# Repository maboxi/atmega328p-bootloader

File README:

# Bootloader + Python program for the Atmega328P chip

This project contains a custom bootloader program for the Atmega328P (known for the Arduino family boards) which fulfills basic bootloader functionalities:
- Uploading a program (given by a Intel Hex format file) to the microcontroller
- Verifiying an upload
- Reading the fuse bytes (extended, high, low) and interpreting the values

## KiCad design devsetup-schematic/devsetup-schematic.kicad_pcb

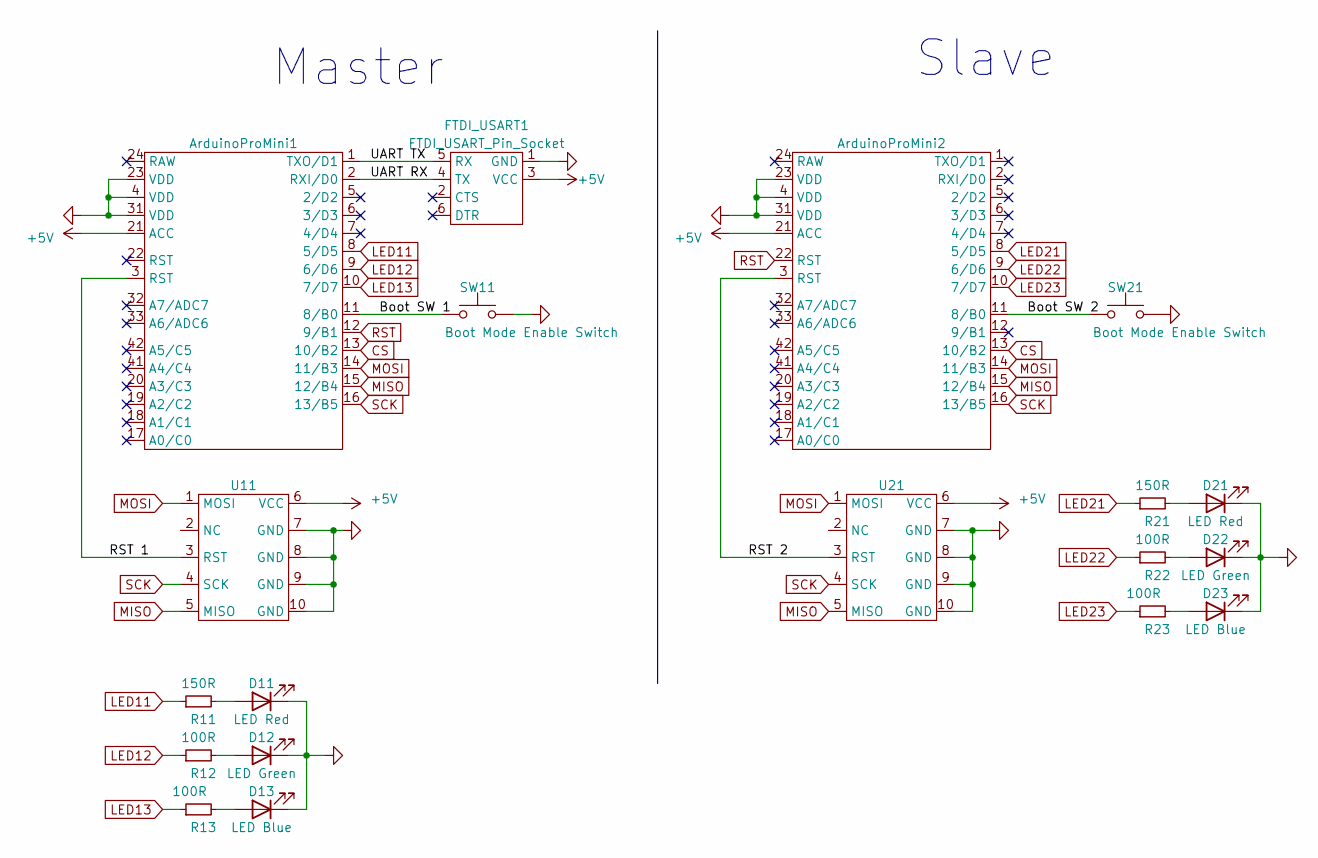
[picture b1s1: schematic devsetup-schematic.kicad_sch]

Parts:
ArduinoProMini1, ArduinoProMini2: ArduinoProMini-PinSockets
D11, D21: LED Red; LED_D5.0mm_FlatTop
D12, D22: LED Green; LED_D5.0mm_FlatTop
D13, D23: LED Blue; LED_D5.0mm_FlatTop
FTDI_USART1: FTDI_USART_Pin_Socket; PinSocket_1x06_P2.54mm_Vertical
R11, R21: 150R; R_Axial_DIN0207_L6.3mm_D2.5mm_P7.62mm_Horizontal
R12, R13, R22, R23: 100R; R_Axial_DIN0207_L6.3mm_D2.5mm_P7.62mm_Horizontal
SW11, SW21: Boot Mode Enable Switch; SW_PUSH_6mm
U11, U21: USBASP_Header_10Pin

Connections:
+5V: ArduinoProMini1.21 (ACC), ArduinoProMini2.21 (ACC), FTDI_USART1.3 (VCC), U11.6 (VCC), U21.6 (VCC)
/Boot SW 1: ArduinoProMini1.11 (8/B0), SW11.1
/Boot SW 2: ArduinoProMini2.11 (8/B0), SW21.1
/RST 1: ArduinoProMini1.3 (RST), U11.3 (RST)
/RST 2: ArduinoProMini2.3 (RST), U21.3 (RST)
/UART RX: ArduinoProMini1.2 (RXI/D0), FTDI_USART1.4 (TX)
/UART TX: ArduinoProMini1.1 (TXO/D1), FTDI_USART1.5 (RX)
CS: ArduinoProMini1.13 (10/B2), ArduinoProMini2.13 (10/B2)
GND: ArduinoProMini1.4 (VDD), ArduinoProMini1.23 (VDD), ArduinoProMini1.31 (VDD), ArduinoProMini2.4 (VDD), ArduinoProMini2.23 (VDD), ArduinoProMini2.31 (VDD), D11.1 (K), D12.1 (K), D13.1 (K), D21.1 (K), D22.1 (K), D23.1 (K), FTDI_USART1.1 (GND), SW11.2, SW21.2, U11.7 (GND), U11.8 (GND), U11.9 (GND), U11.10 (GND), U21.7 (GND), U21.8 (GND), U21.9 (GND), U21.10 (GND)
LED11: ArduinoProMini1.8 (5/D5), R11.1
LED12: ArduinoProMini1.9 (6/D6), R12.1
LED13: ArduinoProMini1.10 (7/D7), R13.1
LED21: ArduinoProMini2.8 (5/D5), R21.1
LED22: ArduinoProMini2.9 (6/D6), R22.1
LED23: ArduinoProMini2.10 (7/D7), R23.1
MISO: ArduinoProMini1.15 (12/B4), ArduinoProMini2.15 (12/B4), U11.5 (MISO), U21.5 (MISO)
MOSI: ArduinoProMini1.14 (11/B3), ArduinoProMini2.14 (11/B3), U11.1 (MOSI), U21.1 (MOSI)
unnamed: D11.2 (A), R11.2
unnamed: D12.2 (A), R12.2
unnamed: D13.2 (A), R13.2
unnamed: D21.2 (A), R21.2
unnamed: D22.2 (A), R22.2
unnamed: D23.2 (A), R23.2
RST: ArduinoProMini1.12 (9/B1), ArduinoProMini2.22 (RST)
SCK: ArduinoProMini1.16 (13/B5), ArduinoProMini2.16 (13/B5), U11.4 (SCK), U21.4 (SCK)

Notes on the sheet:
Master
Slave

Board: 2 copper layers, 19 parts (0 on the bottom side), 25 nets, no tracks yet.

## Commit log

2024-08-18 basic dev board for bootloader testing
2024-08-18 first basic testing for bootloader program: uart com., boot mode enable switch
2024-08-19 python script that will be communicating with the atmega bootloader
2024-08-23 basic bootloader: human friendly UART interaction
2024-08-23 basic README file
2024-08-23 basic readme fileü
2024-08-27 specification diagrams (Modelio 5.4.1 project)
2024-08-27 added first steps for memory verification
2024-08-27 verify cmd: basic setup
2024-08-27 basic memory reading
2024-08-27 memory verification against hex file implemented
2024-08-27 moved example app to bootloader solution
2024-08-27 baseline for uploading: receive data, decode string to bytes, checksum; yet to be tested
2024-08-27 added led slowblink test program
2024-08-28 upload: hex file transmission and checking implemented
2024-08-28 upload: either boot_page_fill_safe() or boot_page_write() doesn't work properly
2024-08-29 decode fuse bytes and print fuse configs
2024-08-29 -fixed verification problem, upload not fully working
2024-08-29 upload works now! switched to ram-based page buffer to minimize spm usage
2024-08-29 added interesting links and useful tips
2024-08-29 QOL changes
2024-08-31 testing serialport rust library for uploader
2024-09-01 rust uploader: rx/tx with bootloader works
2024-09-01 rust uploader: upload and verify now working
